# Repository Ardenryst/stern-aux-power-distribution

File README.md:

# stern-aux-power-distribution
Board to tap into 12V auxilary power connector and offer several options to connect mods

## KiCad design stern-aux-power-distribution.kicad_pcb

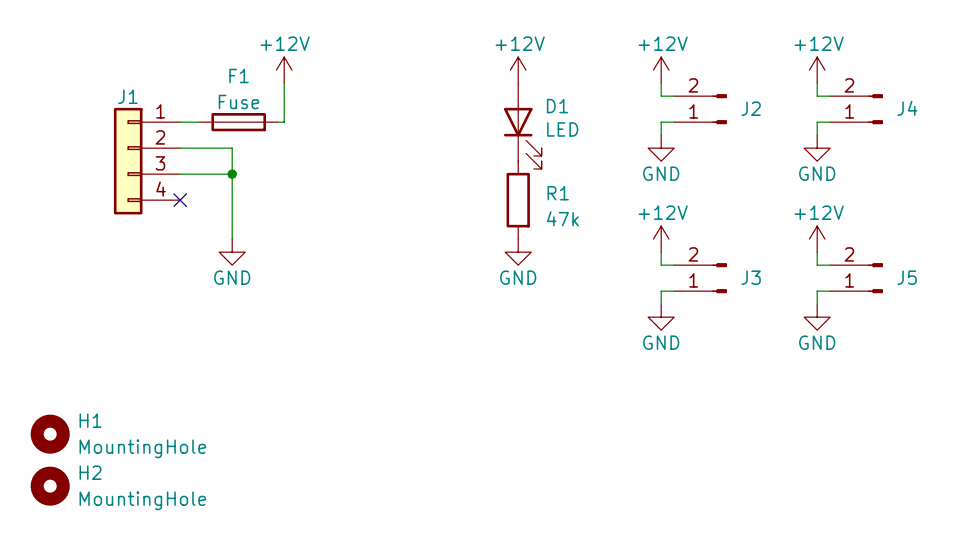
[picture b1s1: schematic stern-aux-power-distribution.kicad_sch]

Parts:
D1: LED; LED_D3.0mm
F1: Fuse; Fuse holder Keystone 3557-2
H1, H2: MountingHole; MountingHole_4.3mm_M4
J1: Conn_01x04; TE_MATE-N-LOK_350211-1_1x04_P5.08mm_Vertical
J2, J3, J4, J5: Conn_01x02_Pin; Molex_KK-254_AE-6410-02A_1x02_P2.54mm_Vertical
R1: 47k; R_Axial_DIN0207_L6.3mm_D2.5mm_P10.16mm_Horizontal

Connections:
+12V: D1.2 (A), F1.2, J2.2, J3.2, J4.2, J5.2
GND: J1.2, J1.3, J2.1, J3.1, J4.1, J5.1, R1.2
unnamed: D1.1 (K), R1.1
unnamed: F1.1, J1.1

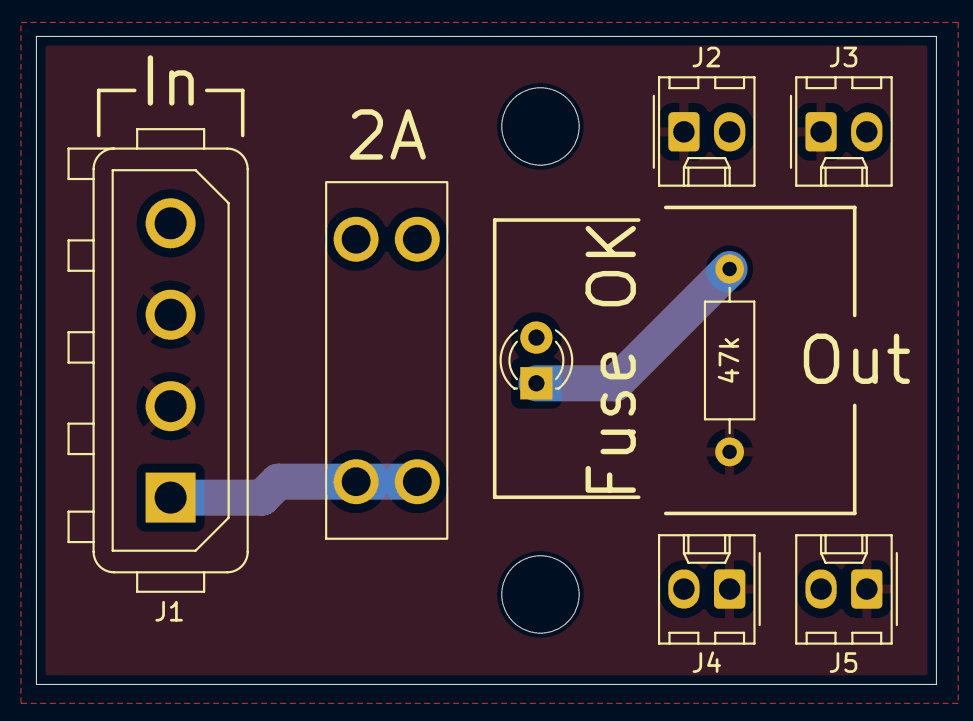
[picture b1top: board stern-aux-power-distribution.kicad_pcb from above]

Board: 2 copper layers, 50.0 x 36.0 mm, 10 parts (0 on the bottom side), 4 nets.

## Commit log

2025-04-28 Design completed
2025-04-29 More silkscreen info
